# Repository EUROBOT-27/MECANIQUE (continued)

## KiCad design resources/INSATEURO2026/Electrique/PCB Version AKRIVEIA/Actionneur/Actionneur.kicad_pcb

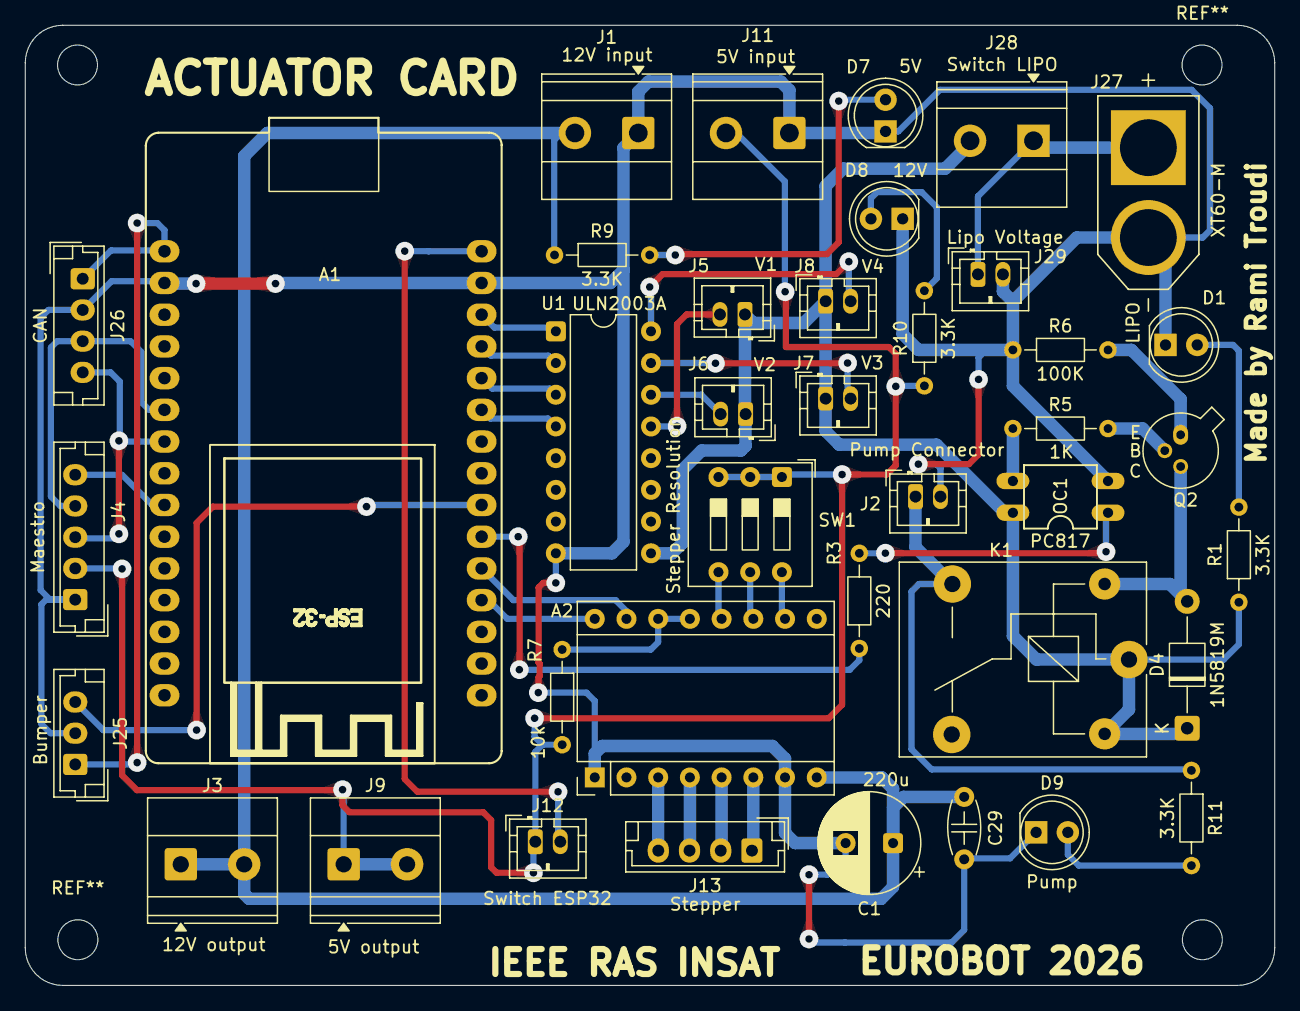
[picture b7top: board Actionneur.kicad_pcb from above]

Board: 2 copper layers, 100.1 x 76.9 mm, 40 parts (0 on the bottom side), 40 nets.

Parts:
A1: ESP32_DevKit_V1_DOIT_30GPIOs; DOIT_ESP32_DEVKIT_30Pins
A2: Pololu_Breakout_DRV8825; Pololu_Breakout-16_15.2x20.3mm
ACTUATOR CARD: MountingHole_3.2mm_M3
C1: 220u; CP_Radial_D8.0mm_P3.80mm
C29: 105; C_Disc_D4.7mm_W2.5mm_P5.00mm
D1: LIPO; LED_D5.0mm
D4: 1N5819M; D_T-1_P10.16mm_Horizontal
D7: 5V; LED_D5.0mm
D8: 12V; LED_D5.0mm
D9: Pump; LED_D5.0mm
J1: 12V input; TerminalBlock_Phoenix_MKDS-1,5-2-5.08_1x02_P5.08mm_Horizont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
J2: Pump Connector; JST_PH_B2B-PH-K_1x02_P2.00mm_Vertical
J3: 12V output; TerminalBlock_Phoenix_MKDS-1,5-2-5.08_1x02_P5.08mm_Horizont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
J4: Maestro; JST_EH_B5B-EH-A_1x05_P2.50mm_Vertical
J5: V1; JST_PH_B2B-PH-K_1x02_P2.00mm_Vertical
J6: V2; JST_PH_B2B-PH-K_1x02_P2.00mm_Vertical
J7: V3; JST_PH_B2B-PH-K_1x02_P2.00mm_Vertical
J8: V4; JST_PH_B2B-PH-K_1x02_P2.00mm_Vertical
J9: 5V output; TerminalBlock_Phoenix_MKDS-1,5-2-5.08_1x02_P5.08mm_Horizont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
J11: 5V input; TerminalBlock_Phoenix_MKDS-1,5-2-5.08_1x02_P5.08mm_Horizont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
J12: Switch ESP32; JST_PH_B2B-PH-K_1x02_P2.00mm_Vertical
J13: Stepper; JST_EH_B4B-EH-A_1x04_P2.50mm_Vertical
J25: Bumper; JST_EH_B3B-EH-A_1x03_P2.50mm_Vertical
J26: CAN; JST_EH_B4B-EH-A_1x04_P2.50mm_Vertical
J27: XT60-M; AMASS_XT60-M
J28: Switch LIPO; TerminalBlock_Phoenix_MKDS-1,5-2-5.08_1x02_P5.08mm_Horizont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
J29: Lipo Voltage; JST_PH_B2B-PH-K_1x02_P2.00mm_Vertical
K1: SANYOU_SRD_Form_C; Relay_SPDT_SANYOU_SRD_Series_Form_C
OC1: PC817; DIL04
Q2: 2N2222A; TO-18-3_EBC
R1, R9, R10, R11: 3.3K; R_Axial_DIN0204_L3.6mm_D1.6mm_P7.62mm_Horizontal
R3: 220; R_Axial_DIN0204_L3.6mm_D1.6mm_P7.62mm_Horizontal
R5: 1K; R_Axial_DIN0204_L3.6mm_D1.6mm_P7.62mm_Horizontal
R6: 100K; R_Axial_DIN0204_L3.6mm_D1.6mm_P7.62mm_Horizontal
R7: 10k; R_Axial_DIN0204_L3.6mm_D1.6mm_P7.62mm_Horizontal
SW1: Stepper Resolution; SW_DIP_SPSTx03_Slide_9.78x9.8mm_W7.62mm_P2.54mm
U1: ULN2003A; DIP-16_W7.62mm

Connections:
12V: A2.8 (VMOT), C1.1, C29.1, J1.2, J3.1, J3.2, R9.1
+3.3V: A1.1 (3.3V), J25.1, J26.1
+5V: J4.2, J9.1, J9.2, J11.2, J12.1, R7.2, R10.1, SW1.1, SW1.2, SW1.3
DIR: A1.19 (ADC1_CH6/D34), A2.16 (DIR)
EV1: J5.2, U1.13 (O4)
EV2: J6.2, U1.14 (O3)
EV3: J7.2, U1.15 (O2)
EV4: J8.2, U1.16 (O1)
GND: A1.2 (GND), A1.29 (GND), A2.1 (GND), A2.7 (GND), C1.2, C29.2, D1.1 (K), D7.1 (K), D8.1 (K), D9.1 (K), J1.1, J2.2, J4.1, J11.1, J25.2, J26.2, J27.N (NEG), J29.2, OC1.2, R6.1, U1.8 (GND)
unnamed: A1.30 (VIN), J12.2
unnamed: A2.4 (A1), J13.3
unnamed: A2.3 (A2), J13.4
unnamed: A2.5 (B1), J13.2
unnamed: A2.6 (B2), J13.1
unnamed: A2.10 (M0), SW1.6
unnamed: A2.11 (M1), SW1.5
unnamed: A2.12 (M2), SW1.4
unnamed: A2.13 (~RST), A2.14 (~SLP), R7.1
unnamed: D1.2 (A), R1.2
unnamed: D4.2 (A), K1.2, Q2.3 (C)
unnamed: D7.2 (A), R9.2
unnamed: D8.2 (A), R10.2
unnamed: D9.2 (A), R11.2
unnamed: J27.P (POS), J28.1, J29.1
unnamed: OC1.1, R3.2
unnamed: OC1.3, R5.1
unnamed: Q2.2 (B), R5.2
unnamed: Q2.1 (E), R6.2
Pump: J2.1, K1.3, R11.1
Pump Signal: A1.21 (ADC1_CH4/D32), R3.1
RST: A1.9 (D18), J4.5
RX: A1.6 (RX2/GPIO16), J4.4, J26.3
SIG: A1.22 (ADC1_CH4/D33), J25.3
STEP: A1.20 (ADC1_CH7/D35), A2.15 (STEP)
TX: A1.7 (TX2/GPIO17), J4.3, J26.4
VDC: D4.1 (K), J5.1, J6.1, J7.1, J8.1, J28.2, K1.1, K1.5, OC1.4, R1.1, U1.9 (COM)
Valve1: A1.25 (ADC2_CH7/D27), U1.4 (I4)
Valve2: A1.26 (ADC2_CH6/D14), U1.3 (I3)
Valve3: A1.27 (ADC2_CH5/D12), U1.2 (I2)
Valve4: A1.28 (ADC2_CH4/D13), U1.1 (I1)
